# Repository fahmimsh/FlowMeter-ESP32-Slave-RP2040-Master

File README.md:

# FlowMeter-ESP32-Slave-RP2040-Master

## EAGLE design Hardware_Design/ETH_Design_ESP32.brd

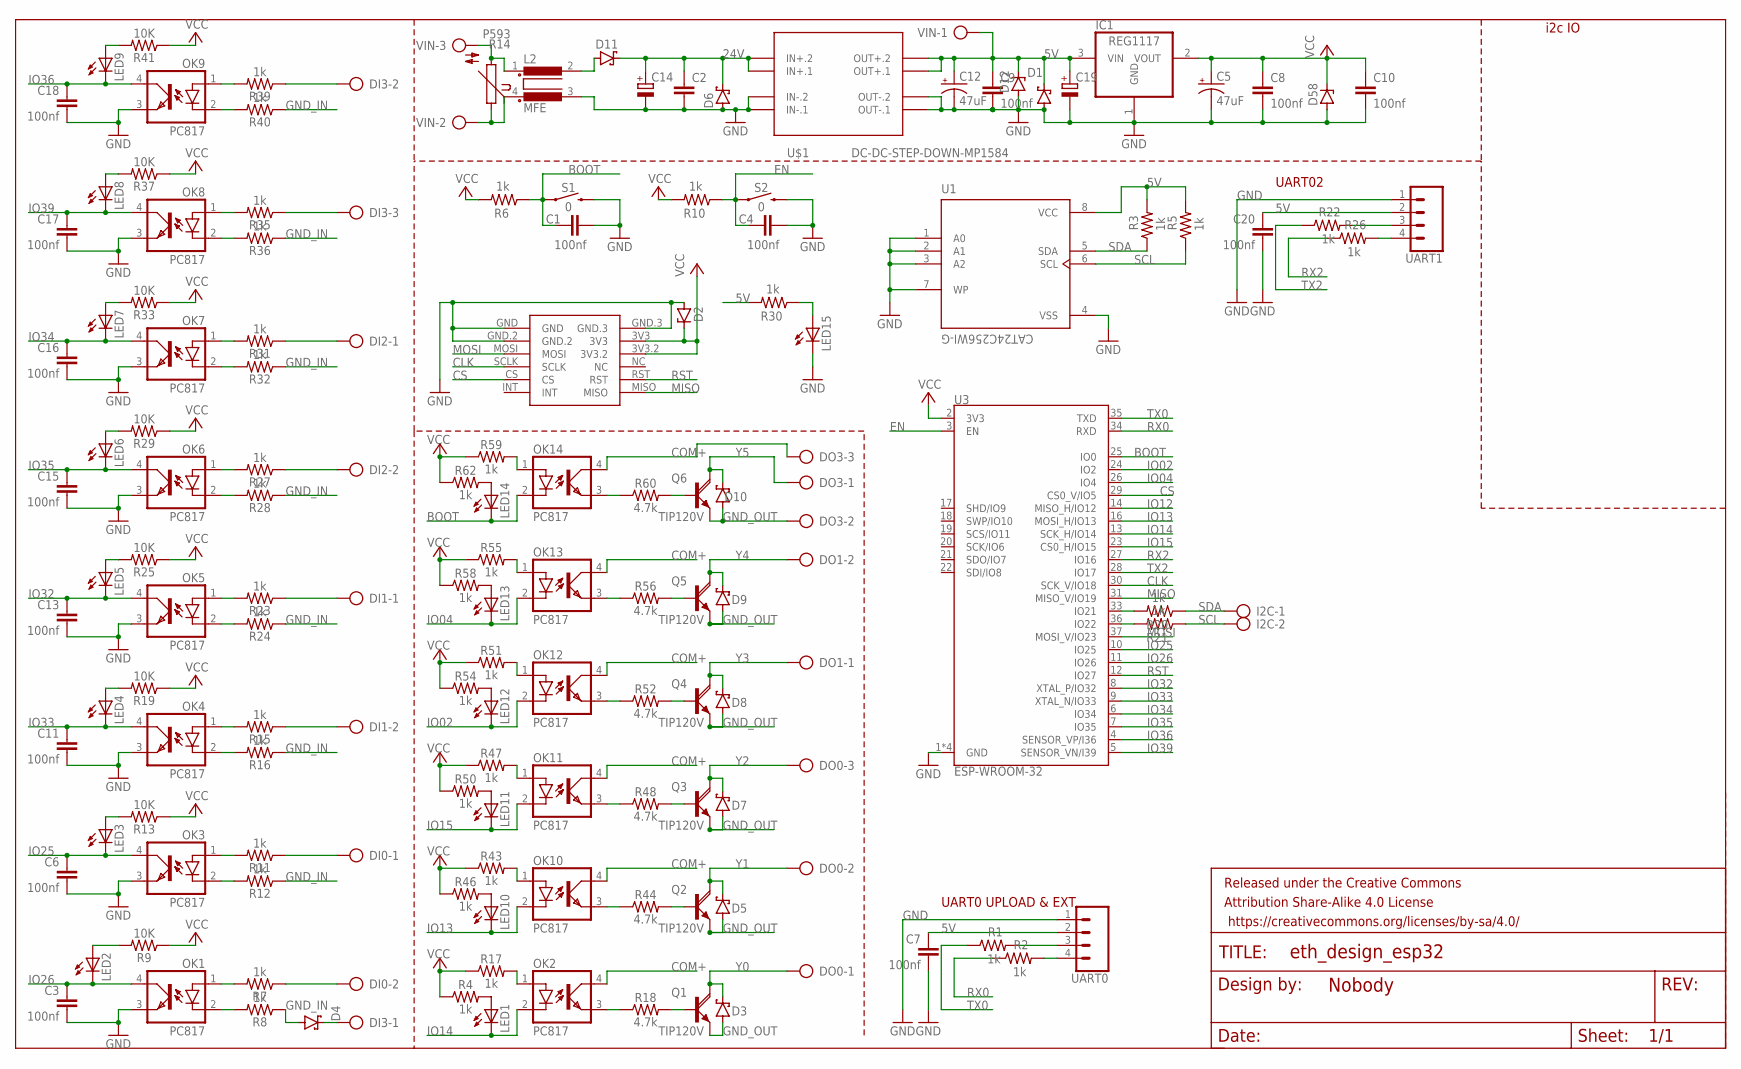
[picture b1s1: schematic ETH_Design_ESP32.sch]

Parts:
C1, C3, C4, C6, C7, C8, C9, C10, C11, C13, C15, C16, C17, C18, C20: 100nf; 0805
C2: C-EUC1206K; C1206K
C5, C12: 47uF; EIA3528
C14, C19: CPOL-EUE2.5-7; E2,5-7
D1, D3, D4, D5, D6, D7, D8, D9, D10, D11: SCHOTTKY-DIODESMD; SMB
D2, D12, D58: ZENER-DIODESOD80C; SOD80C
DI0, DI1, DI2: AK500/2
DI3: AK500/3
DO0, DO3: AK500/3
DO1: AK500/2
FRAME1: FRAME-LETTERNO_PACKAGE; DUMMY
I2C: AK500/2
IC1: REG1117; SOT223
L2: MFE
LED1, LED2, LED3, LED4, LED5, LED6, LED7, LED8, LED9, LED10, LED11, LED12, LED13, LED14, LED15: LEDCHIPLED_0805; CHIPLED_0805
OK1, OK2, OK3, OK4, OK5, OK6, OK7, OK8, OK9, OK10, OK11, OK12, OK13, OK14: PC817; DIL04
Q1, Q2, Q3, Q4, Q5, Q6: TIP120V; TO220AV
R1, R2, R3, R4, R5, R6, R7, R8, R10, R11, R12, R15, R16, R17, R20, R21, R22, R23, R24, R26, R27, R28, R30, R31, R32, R35, R36, R39, R40, R43, R46, R47, R50, R51, R54, R55, R58, R59, R62: 1k; 0805
R9, R13, R19, R25, R29, R33, R37, R41: 10K; 0805
R14: P593
R18, R44, R48, R52, R56, R60: 4.7k; 0805
S1, S2: 0; TACTILE_SWITCH_PTH_6.0MM_KIT
U1: CAT24C256WI-G; SOIC127P600X175-8N
U3: ESP-WROOM-32
U$1: DC-DC-STEP-DOWN-MP1584
U$2: MINI_W5500
UART0, UART1: CONN_04POLAR; MOLEX-1X4
VIN: AK500/3

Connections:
5V: C7.1, C9.1, C12.A (+), C19.+, C20.1, D1.C, D12.C, IC1.3 (VIN), R3.2, R5.2, R30.2, U1.8 (VCC), U$1.OUT+.1, U$1.OUT+.2, UART0.2, UART1.2, VIN.1
24V: C2.1, C14.+, D6.C, D11.C, U$1.IN+.1, U$1.IN+.2
BOOT: C1.2, LED14.C, OK14.2 (C), R6.1, S1.1, U3.25 (IO0)
CLK: U3.30 (SCK_V/IO18), U$2.SCLK
COM+: DO3.3, OK2.4 (COL), OK10.4 (COL), OK11.4 (COL), OK12.4 (COL), OK13.4 (COL), OK14.4 (COL)
CS: U3.29 (CS0_V/IO5), U$2.CS
EN: C4.2, R10.1, S2.1, U3.3 (EN)
GND: C1.1, C2.2, C3.2, C4.1, C5.C (-), C6.2, C7.2, C8.2, C9.2, C10.2, C11.2, C12.C (-), C13.2, C14.-, C15.2, C16.2, C17.2, C18.2, C19.-, C20.2, D1.A, D2.A, D6.A, D12.A, D58.A, IC1.1 (GND), L2.3 (4), LED15.C, OK1.3 (EMIT), OK3.3 (EMIT), OK4.3 (EMIT), OK5.3 (EMIT), OK6.3 (EMIT), OK7.3 (EMIT), OK8.3 (EMIT), OK9.3 (EMIT), S1.3 (2), S2.3 (2), U1.1 (A0), U1.2 (A1), U1.3 (A2), U1.4 (VSS), U1.7 (WP), U3.1 (GND), U3.15 (GND), U3.38 (GND), U3.GND, U$1.IN-.1, U$1.IN-.2, U$1.OUT-.1, U$1.OUT-.2, U$2.GND, U$2.GND.2, U$2.GND.3, UART0.1, UART1.1
GND_IN: D4.A, R8.1, R12.1, R16.1, R24.1, R28.1, R32.1, R36.1, R40.1
GND_OUT: D3.A, D5.A, D7.A, D8.A, D9.A, D10.A, DO3.2, Q1.E, Q2.E, Q3.E, Q4.E, Q5.E, Q6.E
IO02: LED12.C, OK12.2 (C), U3.24 (IO2)
IO04: LED13.C, OK13.2 (C), U3.26 (IO4)
IO12: U3.14 (MISO_H/IO12)
IO13: LED10.C, OK10.2 (C), U3.16 (MOSI_H/IO13)
IO14: LED1.C, OK2.2 (C), U3.13 (SCK_H/IO14)
IO15: LED11.C, OK11.2 (C), U3.23 (CS0_H/IO15)
IO25: C6.1, LED3.C, OK3.4 (COL), U3.10 (IO25)
IO26: C3.1, LED2.C, OK1.4 (COL), U3.11 (IO26)
IO32: C13.1, LED5.C, OK5.4 (COL), U3.8 (XTAL_P/IO32)
IO33: C11.1, LED4.C, OK4.4 (COL), U3.9 (XTAL_N/IO33)
IO34: C16.1, LED7.C, OK7.4 (COL), U3.6 (IO34)
IO35: C15.1, LED6.C, OK6.4 (COL), U3.7 (IO35)
IO36: C18.1, LED9.C, OK9.4 (COL), U3.4 (SENSOR_VP/I36)
IO39: C17.1, LED8.C, OK8.4 (COL), U3.5 (SENSOR_VN/I39)
MISO: U3.31 (MISO_V/IO19), U$2.MISO
MOSI: U3.37 (MOSI_V/IO23), U$2.MOSI
unnamed: R1.2, UART0.3
unnamed: R2.2, UART0.4
unnamed: R22.2, UART1.3
unnamed: OK1.1 (A), R7.2
unnamed: L2.1, R14.2, VIN.3
unnamed: L2.4 (3), R14.1, VIN.2
unnamed: OK2.1 (A), R17.2
unnamed: LED1.A, R4.2
unnamed: LED8.A, R37.2
unnamed: OK1.2 (C), R8.2
unnamed: LED7.A, R33.2
unnamed: LED6.A, R29.2
unnamed: LED5.A, R25.2
unnamed: R26.2, UART1.4
unnamed: LED15.A, R30.1
unnamed: OK3.1 (A), R11.2
unnamed: OK2.3 (EMIT), R18.1
unnamed: D11.A, L2.2
unnamed: OK3.2 (C), R12.2
unnamed: LED2.A, R9.2
unnamed: LED3.A, R13.2
unnamed: OK4.1 (A), R15.2
unnamed: OK4.2 (C), R16.2
unnamed: LED4.A, R19.2
unnamed: R20.2, U3.33 (IO21)
unnamed: R21.2, U3.36 (IO22)
unnamed: OK5.1 (A), R23.2
unnamed: OK5.2 (C), R24.2
unnamed: OK6.1 (A), R27.2
unnamed: OK6.2 (C), R28.2
unnamed: OK7.1 (A), R31.2
unnamed: OK7.2 (C), R32.2
unnamed: OK8.1 (A), R35.2
unnamed: OK8.2 (C), R36.2
unnamed: OK9.1 (A), R39.2
unnamed: OK9.2 (C), R40.2
unnamed: DI0.2, R7.1
unnamed: Q1.B, R18.2
unnamed: OK10.3 (EMIT), R44.1
unnamed: OK10.1 (A), R43.2
unnamed: LED10.A, R46.2
unnamed: Q2.B, R44.2
unnamed: OK11.3 (EMIT), R48.1
unnamed: OK11.1 (A), R47.2
unnamed: LED11.A, R50.2
unnamed: Q3.B, R48.2
unnamed: OK12.3 (EMIT), R52.1
unnamed: OK12.1 (A), R51.2
unnamed: LED12.A, R54.2
unnamed: LED9.A, R41.2
unnamed: Q4.B, R52.2
unnamed: OK13.3 (EMIT), R56.1
unnamed: DI0.1, R11.1
unnamed: OK13.1 (A), R55.2
unnamed: LED13.A, R58.2
unnamed: DI1.2, R15.1
unnamed: Q5.B, R56.2
unnamed: OK14.3 (EMIT), R60.1
unnamed: DI1.1, R23.1
unnamed: OK14.1 (A), R59.2
unnamed: LED14.A, R62.2
unnamed: DI2.2, R27.1
unnamed: Q6.B, R60.2
unnamed: DI2.1, R31.1
unnamed: DI3.3, R35.1
unnamed: DI3.2, R39.1
unnamed: D4.C, DI3.1
RST: U3.12 (IO27), U$2.RST
RX0: R2.1, U3.34 (RXD)
RX2: R26.1, U3.27 (IO16)
SCL: I2C.2, R5.1, R21.1, U1.6 (SCL)
SDA: I2C.1, R3.1, R20.1, U1.5 (SDA)
TX0: R1.1, U3.35 (TXD)
TX2: R22.1, U3.28 (IO17)
VCC: C5.A (+), C8.1, C10.1, D2.C, D58.C, IC1.2 (VOUT), R4.1, R6.2, R9.1, R10.2, R13.1, R17.1, R19.1, R25.1, R29.1, R33.1, R37.1, R41.1, R43.1, R46.1, R47.1, R50.1, R51.1, R54.1, R55.1, R58.1, R59.1, R62.1, U3.2 (3V3), U$2.3V3, U$2.3V3.2
Y0: D3.C, DO0.1, Q1.C
Y1: D5.C, DO0.2, Q2.C
Y2: D7.C, DO0.3, Q3.C
Y3: D8.C, DO1.1, Q4.C
Y4: D9.C, DO1.2, Q5.C
Y5: D10.C, DO3.1, Q6.C

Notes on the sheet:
UART0 UPLOAD & EXT
i2c IO
UART02

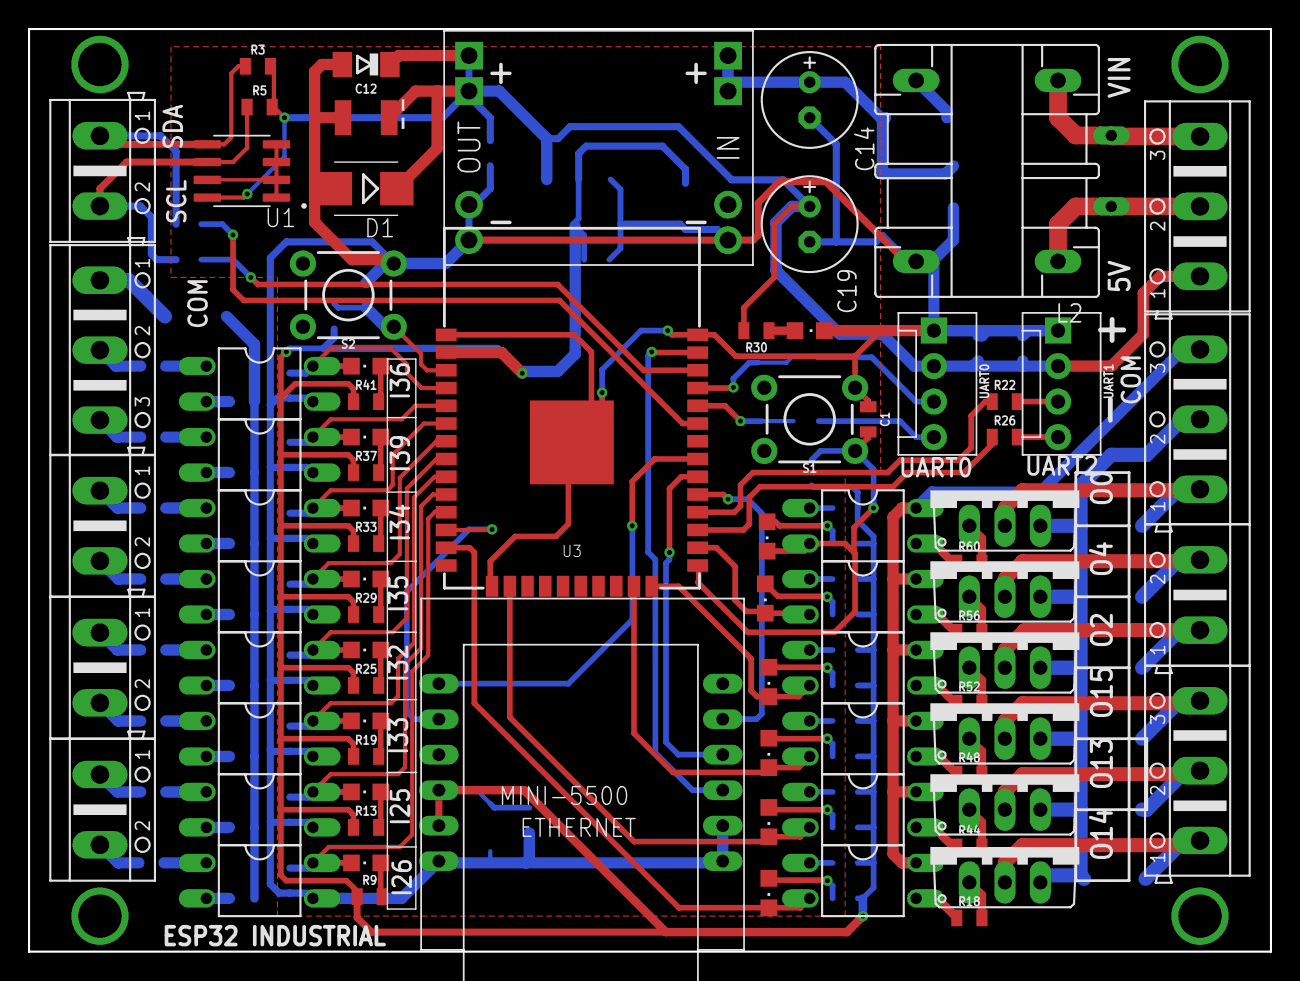
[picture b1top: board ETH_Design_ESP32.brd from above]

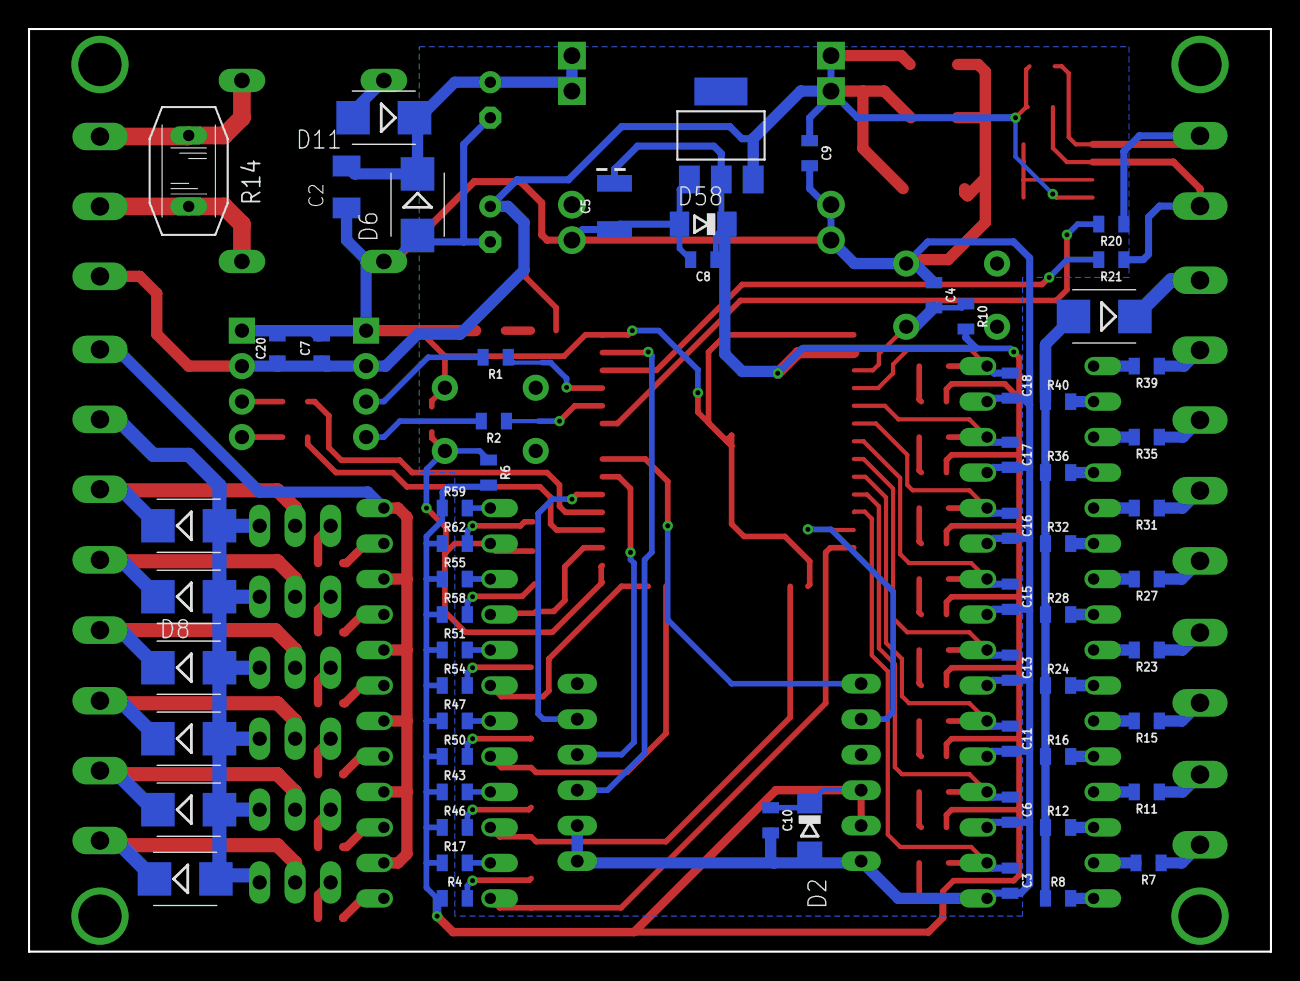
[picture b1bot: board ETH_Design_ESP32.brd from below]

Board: 2 copper layers, 88.9 x 66.0 mm, 142 parts (63 on the bottom side), 106 nets.

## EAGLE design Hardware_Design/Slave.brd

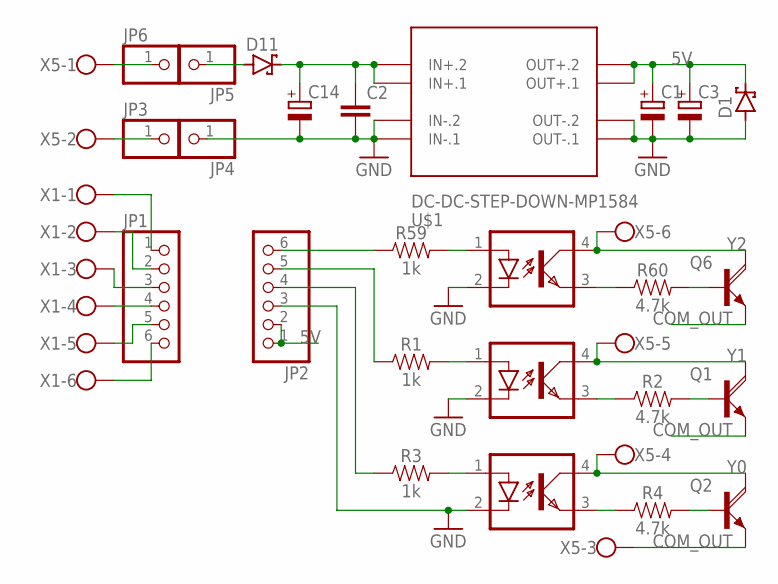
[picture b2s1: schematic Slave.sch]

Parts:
C1, C3, C14: CPOL-EUE2.5-7; E2,5-7
C2: C-EUC1206K; C1206K
D1, D11: SCHOTTKY-DIODESMD; SMB
JP1, JP2: PINHD-1X6B; 1X06-BIG
JP3, JP4, JP5, JP6: PINHD-1X1; 1X01
OK1, OK2, OK14: PC817; DIL04
Q1, Q2, Q6: TIP120V; TO220AV
R1, R3, R59: 1k; 0805
R2, R4, R60: 4.7k; 0805
U$1: DC-DC-STEP-DOWN-MP1584
X1, X5: W237-136

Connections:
5V: C1.+, C3.+, D1.C, JP2.1, JP2.2, U$1.OUT+.1, U$1.OUT+.2
COM_OUT: Q1.E, Q2.E, Q6.E, X5.3
GND: C1.-, C2.2, C3.-, C14.-, D1.A, JP2.3, JP4.1, OK1.2 (C), OK2.2 (C), OK14.2 (C), U$1.IN-.1, U$1.IN-.2, U$1.OUT-.1, U$1.OUT-.2
unnamed: OK1.3 (EMIT), R2.1
unnamed: OK1.1 (A), R1.2
unnamed: Q1.B, R2.2
unnamed: OK2.3 (EMIT), R4.1
unnamed: OK2.1 (A), R3.2
unnamed: Q2.B, R4.2
unnamed: JP1.6, X1.6
unnamed: JP1.5, X1.5
unnamed: JP1.4, X1.4
unnamed: JP1.3, X1.3
unnamed: JP1.2, X1.2
unnamed: JP1.1, X1.1
unnamed: JP2.6, R59.1
unnamed: JP2.5, R1.1
unnamed: JP2.4, R3.1
unnamed: D11.A, JP5.1
unnamed: JP3.1, X5.2
unnamed: JP6.1, X5.1
unnamed: C2.1, C14.+, D11.C, U$1.IN+.1, U$1.IN+.2
unnamed: OK14.3 (EMIT), R60.1
unnamed: OK14.1 (A), R59.2
unnamed: Q6.B, R60.2
Y0: OK2.4 (COL), Q2.C, X5.4
Y1: OK1.4 (COL), Q1.C, X5.5
Y2: OK14.4 (COL), Q6.C, X5.6

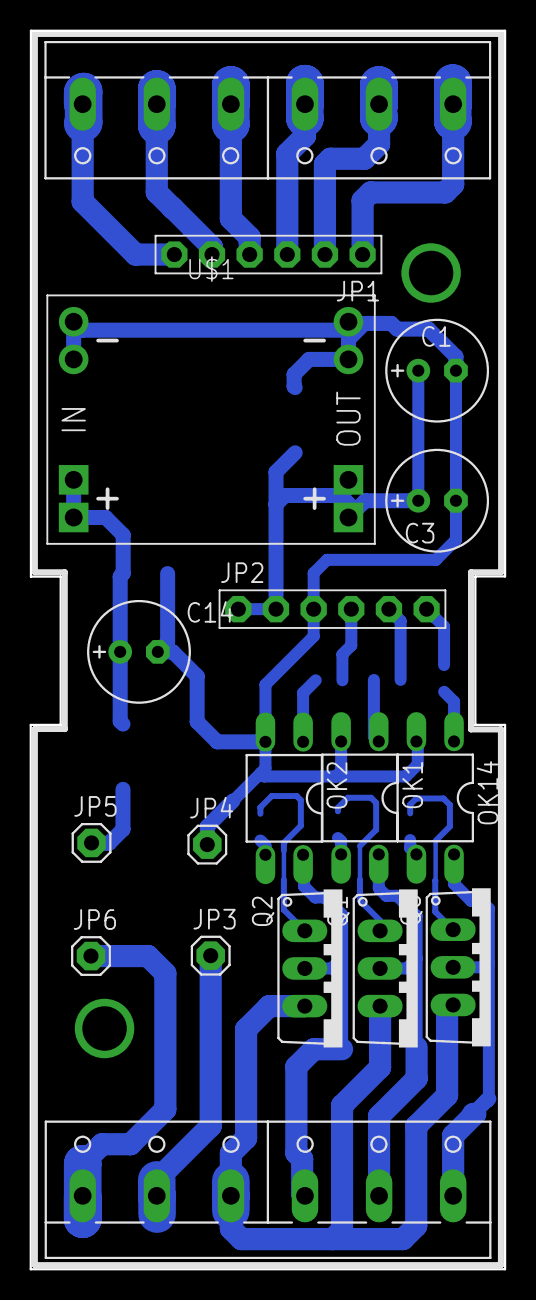
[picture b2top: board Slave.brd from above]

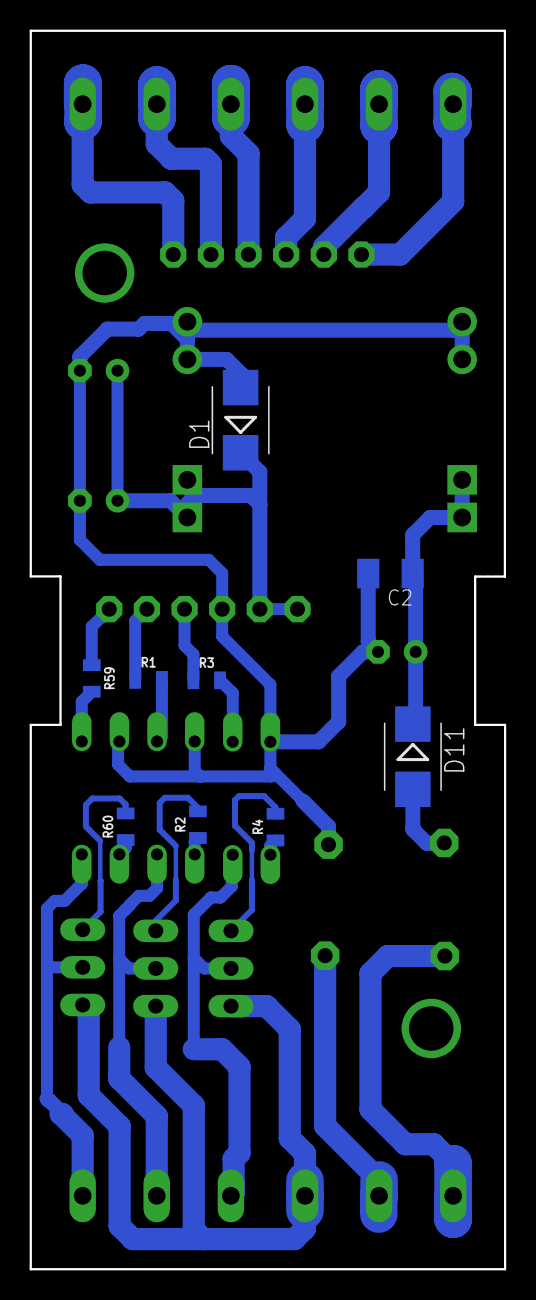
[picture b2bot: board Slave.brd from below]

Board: 2 copper layers, 32.0 x 83.6 mm, 27 parts (9 on the bottom side), 28 nets.

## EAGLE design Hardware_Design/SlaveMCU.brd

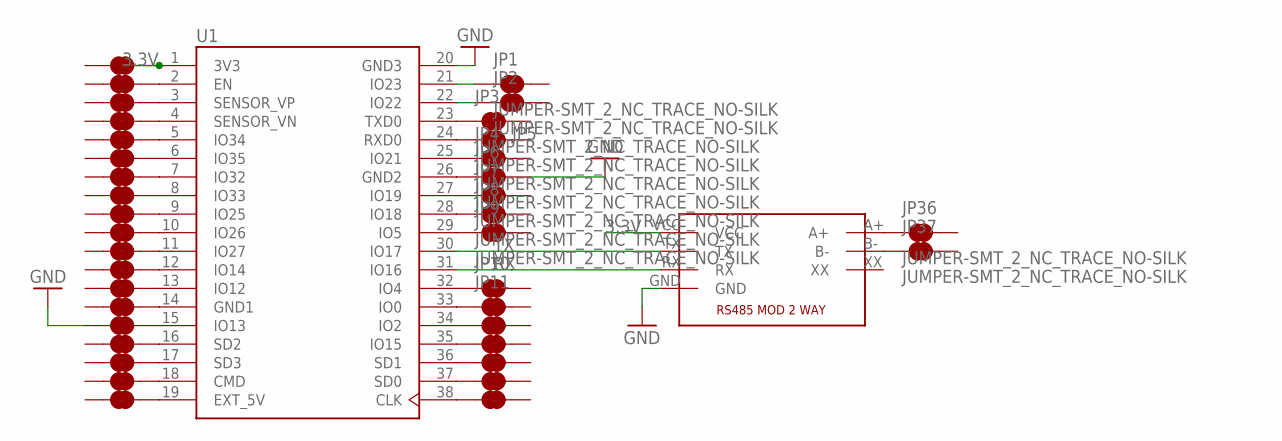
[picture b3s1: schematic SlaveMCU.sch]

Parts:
JP1, JP2, JP3, JP4, JP5, JP6, JP7, JP8, JP9, JP10, JP11, JP12, JP13, JP14, JP15, JP16, JP17, JP18, JP19, JP20, JP21, JP22, JP23, JP24, JP25, JP26, JP27, JP28, JP29, JP30, JP31, JP32, JP33, JP34, JP35, JP36, JP37: JUMPER-SMT_2_NC_TRACE_NO-SILK; SMT-JUMPER_2_NC_TRACE_NO-SILK
U1: ESP32-DEVKITC-32D; MODULE_ESP32-DEVKITC-32D
U$2: RS485_MODULE

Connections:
3.3V: JP35.2, U1.1 (3V3), U$2.VCC
GND: JP6.2, JP21.1, U1.20 (GND3), U$2.GND
unnamed: JP1.1, U1.21 (IO23)
unnamed: JP4.1, U1.25 (IO21)
unnamed: JP5.1, U1.24 (RXD0)
unnamed: JP6.1, U1.26 (GND2)
unnamed: JP7.1, U1.27 (IO19)
unnamed: JP9.1, U1.29 (IO5)
unnamed: JP10.1, U1.32 (IO4)
unnamed: JP11.1, U1.33 (IO0)
unnamed: JP12.1, U1.34 (IO2)
unnamed: JP13.1, U1.35 (IO15)
unnamed: JP14.1, U1.36 (SD1)
unnamed: JP15.1, U1.37 (SD0)
unnamed: JP16.1, U1.38 (CLK)
unnamed: JP17.2, U1.19 (EXT_5V)
unnamed: JP18.2, U1.18 (CMD)
unnamed: JP19.2, U1.17 (SD3)
unnamed: JP20.2, U1.16 (SD2)
unnamed: JP21.2, U1.15 (IO13)
unnamed: JP22.2, U1.14 (GND1)
unnamed: JP23.2, U1.13 (IO12)
unnamed: JP24.2, U1.12 (IO14)
unnamed: JP26.2, U1.10 (IO26)
unnamed: JP27.2, U1.9 (IO25)
unnamed: JP28.2, U1.8 (IO33)
unnamed: JP29.2, U1.7 (IO32)
unnamed: JP30.2, U1.5 (IO34)
unnamed: JP31.2, U1.6 (IO35)
unnamed: JP32.2, U1.4 (SENSOR_VN)
unnamed: JP33.2, U1.3 (SENSOR_VP)
unnamed: JP34.2, U1.2 (EN)
unnamed: JP25.2, U1.11 (IO27)
unnamed: JP8.1, U1.28 (IO18)
unnamed: JP3.1, U1.23 (TXD0)
unnamed: JP2.1, U1.22 (IO22)
unnamed: JP36.1, U$2.A+
unnamed: JP37.1, U$2.B-
RX: U1.31 (IO16), U$2.RX
TX: U1.30 (IO17), U$2.TX

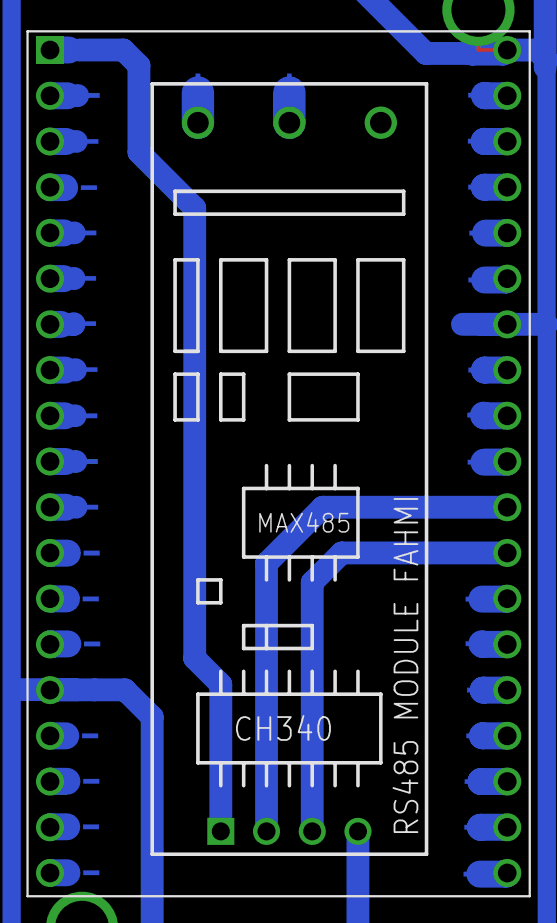
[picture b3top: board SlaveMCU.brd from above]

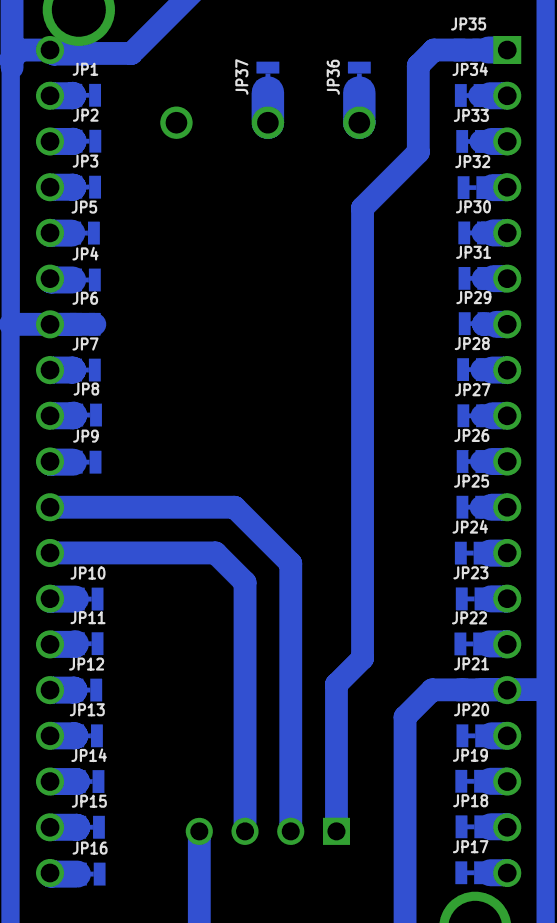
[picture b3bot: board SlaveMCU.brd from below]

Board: 2 copper layers, 39 parts (37 on the bottom side), 40 nets.

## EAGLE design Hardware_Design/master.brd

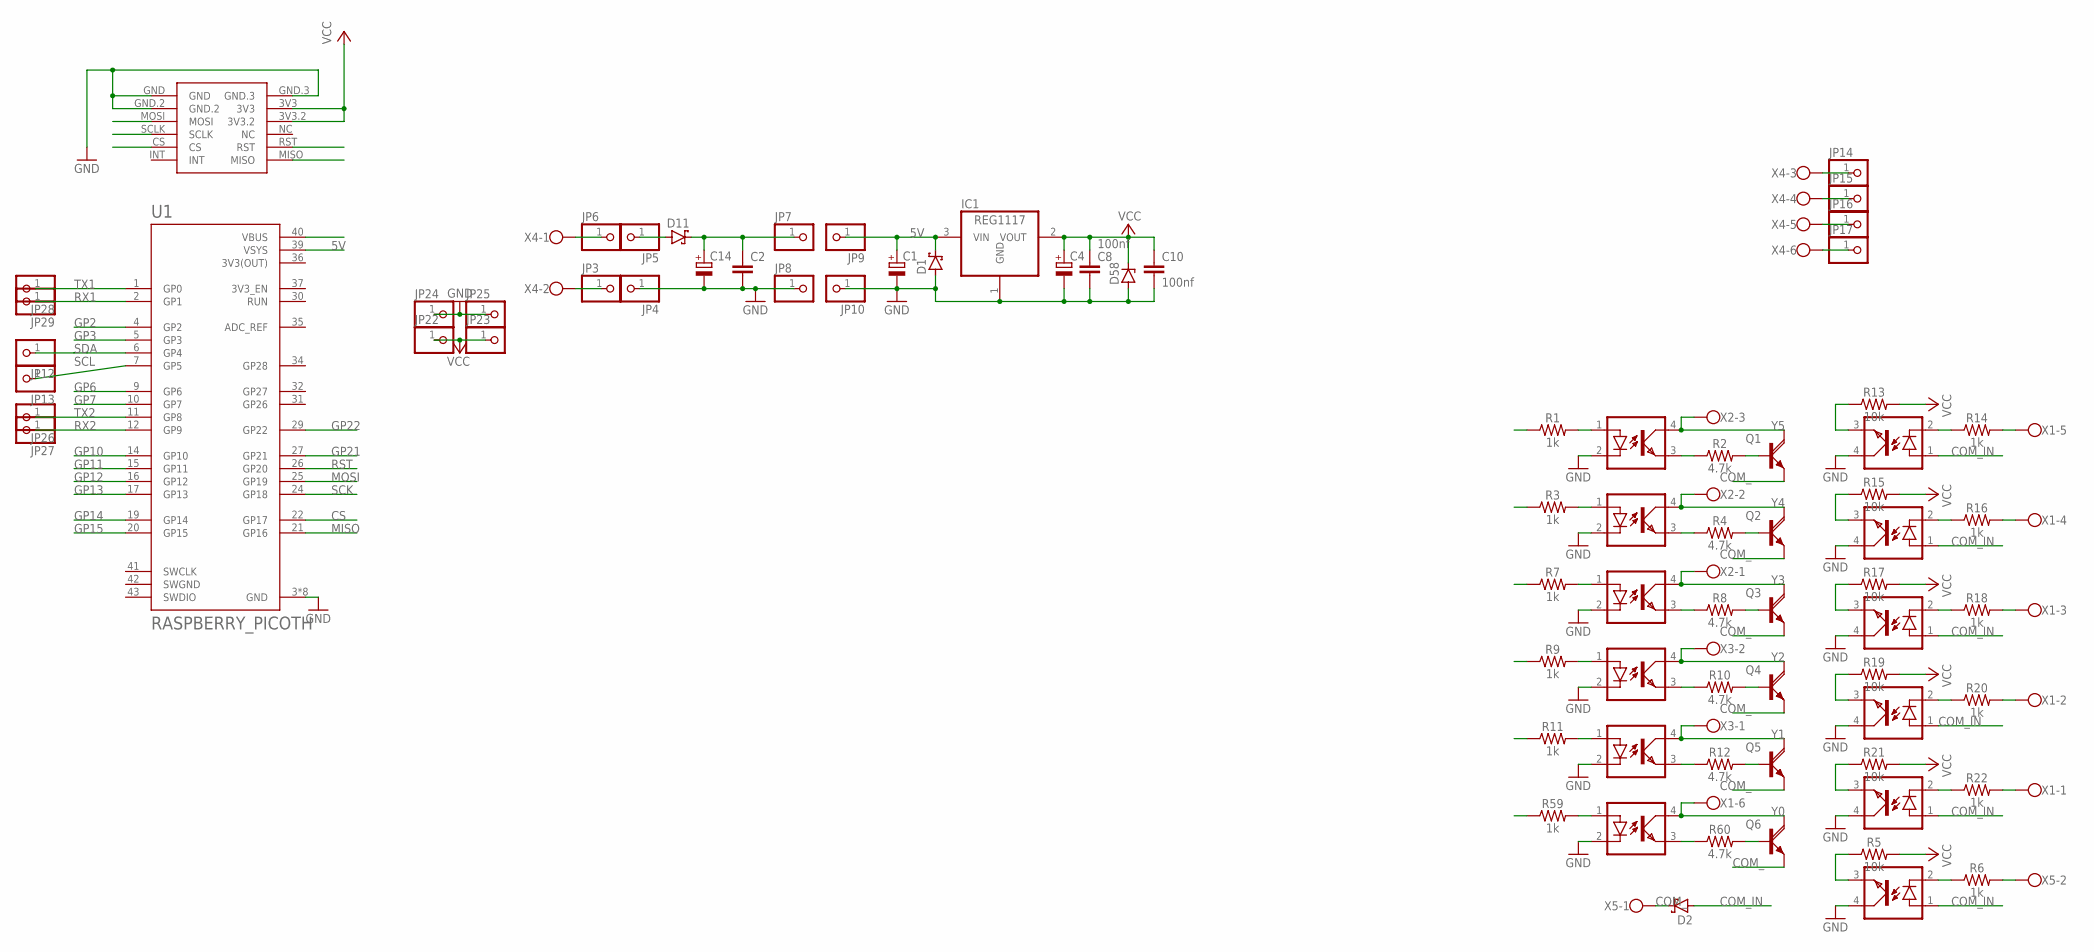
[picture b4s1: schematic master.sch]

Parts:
C1, C4, C14: CPOL-EUE2.5-7; E2,5-7
C2: C-EUC1206K; C1206K
C8, C10: 100nf; 0805
D1, D2, D11: SCHOTTKY-DIODESMD; SMB
D58: ZENER-DIODESOD80C; SOD80C
IC1: REG1117; SOT223
JP3, JP4, JP5, JP6, JP7, JP8, JP9, JP10, JP12, JP13, JP14, JP15, JP16, JP17, JP22, JP23, JP24, JP25, JP26, JP27, JP28, JP29: PINHD-1X1; 1X01
OK1, OK2, OK3, OK4, OK5, OK6, OK7, OK8, OK9, OK10, OK11, OK14: PC817; DIL04
Q1, Q2, Q3, Q4, Q5, Q6: TIP120V; TO220AV
R1, R3, R6, R7, R9, R11, R14, R16, R18, R20, R22, R59: 1k; 0805
R2, R4, R8, R10, R12, R60: 4.7k; 0805
R5, R13, R15, R17, R19, R21: 10k; 0805
U1: RASPBERRY_PICOTH; PICO-PKG-TH
U$2: MINI_W5500
X1, X4: W237-136
X2: W237-103
X3, X5: W237-102

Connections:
3V3(OUT): U1.36 (3V3(OUT))
5V: C1.+, D1.C, IC1.3 (VIN), JP9.1, U1.39 (VSYS)
COM_: D2.C, Q1.E, Q2.E, Q3.E, Q4.E, Q5.E, Q6.E, X5.1
COM_IN: D2.A, OK3.1 (A), OK7.1 (A), OK8.1 (A), OK9.1 (A), OK10.1 (A), OK11.1 (A)
CS: U1.22 (GP17)
GND: C1.-, C2.2, C4.-, C8.2, C10.2, C14.-, D1.A, D58.A, IC1.1 (GND), JP4.1, JP8.1, JP10.1, JP24.1, JP25.1, OK1.2 (C), OK2.2 (C), OK3.4 (COL), OK4.2 (C), OK5.2 (C), OK6.2 (C), OK7.4 (COL), OK8.4 (COL), OK9.4 (COL), OK10.4 (COL), OK11.4 (COL), OK14.2 (C), U1.3 (GND), U1.8 (GND), U1.13 (GND), U1.18 (GND), U1.23 (GND), U1.28 (GND), U1.33 (GND), U1.38 (GND), U$2.GND, U$2.GND.2, U$2.GND.3
GP2: U1.4 (GP2)
GP3: U1.5 (GP3)
GP6: U1.9 (GP6)
GP7: U1.10 (GP7)
GP10: U1.14 (GP10)
GP11: U1.15 (GP11)
GP12: U1.16 (GP12)
GP13: U1.17 (GP13)
GP14: U1.19 (GP14)
GP15: U1.20 (GP15)
GP21: U1.27 (GP21)
GP22: U1.29 (GP22)
MISO: U1.21 (GP16)
MOSI: U1.25 (GP19)
unnamed: OK1.3 (EMIT), R2.1
unnamed: OK1.1 (A), R1.2
unnamed: Q1.B, R2.2
unnamed: OK2.3 (EMIT), R4.1
unnamed: OK2.1 (A), R3.2
unnamed: Q2.B, R4.2
unnamed: OK8.2 (C), R16.1
unnamed: OK9.2 (C), R18.1
unnamed: OK4.3 (EMIT), R8.1
unnamed: OK4.1 (A), R7.2
unnamed: Q3.B, R8.2
unnamed: OK5.3 (EMIT), R10.1
unnamed: OK5.1 (A), R9.2
unnamed: Q4.B, R10.2
unnamed: OK6.3 (EMIT), R12.1
unnamed: JP6.1, X4.1
unnamed: D11.A, JP5.1
unnamed: JP3.1, X4.2
unnamed: OK6.1 (A), R11.2
unnamed: Q5.B, R12.2
unnamed: C2.1, C14.+, D11.C, JP7.1
unnamed: OK7.2 (C), R14.1
unnamed: OK10.2 (C), R20.1
unnamed: OK11.2 (C), R22.1
unnamed: OK3.2 (C), R6.1
unnamed: OK7.3 (EMIT), R13.1
unnamed: OK8.3 (EMIT), R15.1
unnamed: OK9.3 (EMIT), R17.1
unnamed: OK10.3 (EMIT), R19.1
unnamed: JP14.1, X4.3
unnamed: JP15.1, X4.4
unnamed: JP16.1, X4.5
unnamed: JP17.1, X4.6
unnamed: OK11.3 (EMIT), R21.1
unnamed: OK3.3 (EMIT), R5.1
unnamed: R14.2, X1.5
unnamed: R16.2, X1.4
unnamed: R18.2, X1.3
unnamed: R20.2, X1.2
unnamed: R22.2, X1.1
unnamed: R6.2, X5.2
unnamed: OK14.3 (EMIT), R60.1
unnamed: OK14.1 (A), R59.2
unnamed: Q6.B, R60.2
RST: U1.26 (GP20)
RX1: JP29.1, U1.2 (GP1)
RX2: JP27.1, U1.12 (GP9)
SCK: U1.24 (GP18)
SCL: JP13.1, U1.7 (GP5)
SDA: JP12.1, U1.6 (GP4)
SWGND: U1.42 (SWGND)
TX1: JP28.1, U1.1 (GP0)
TX2: JP26.1, U1.11 (GP8)
VCC: C4.+, C8.1, C10.1, D58.C, IC1.2 (VOUT), JP22.1, JP23.1, R5.2, R13.2, R15.2, R17.2, R19.2, R21.2, U$2.3V3, U$2.3V3.2
Y0: OK14.4 (COL), Q6.C, X1.6
Y1: OK6.4 (COL), Q5.C, X3.1
Y2: OK5.4 (COL), Q4.C, X3.2
Y3: OK4.4 (COL), Q3.C, X2.1
Y4: OK2.4 (COL), Q2.C, X2.2
Y5: OK1.4 (COL), Q1.C, X2.3

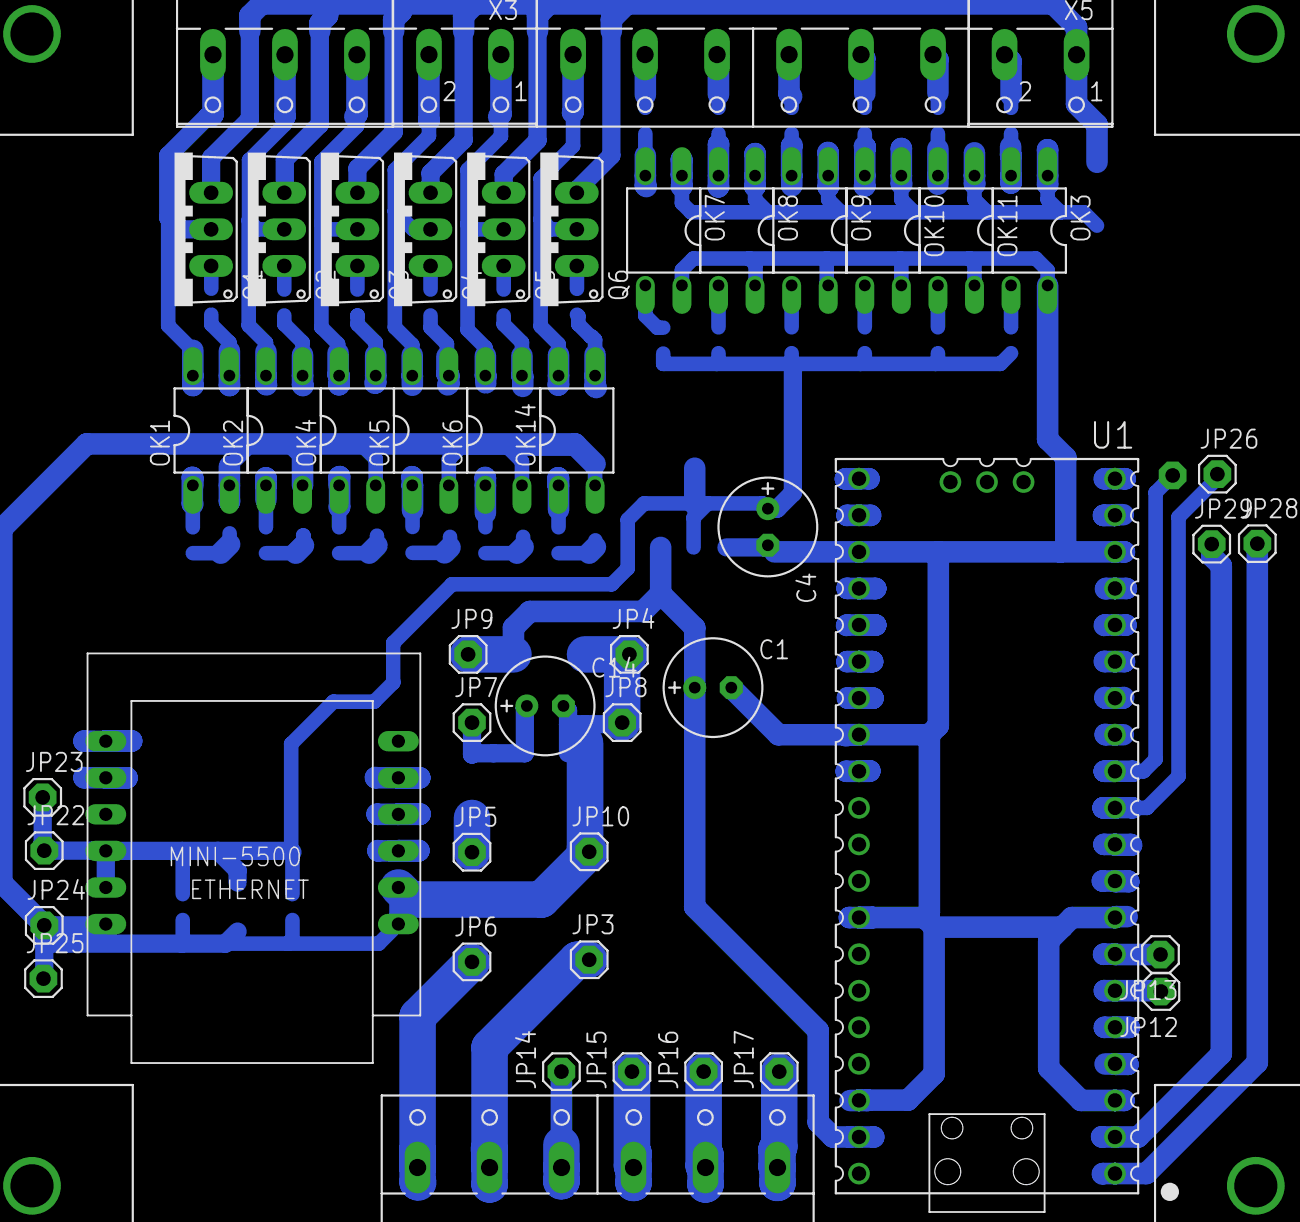
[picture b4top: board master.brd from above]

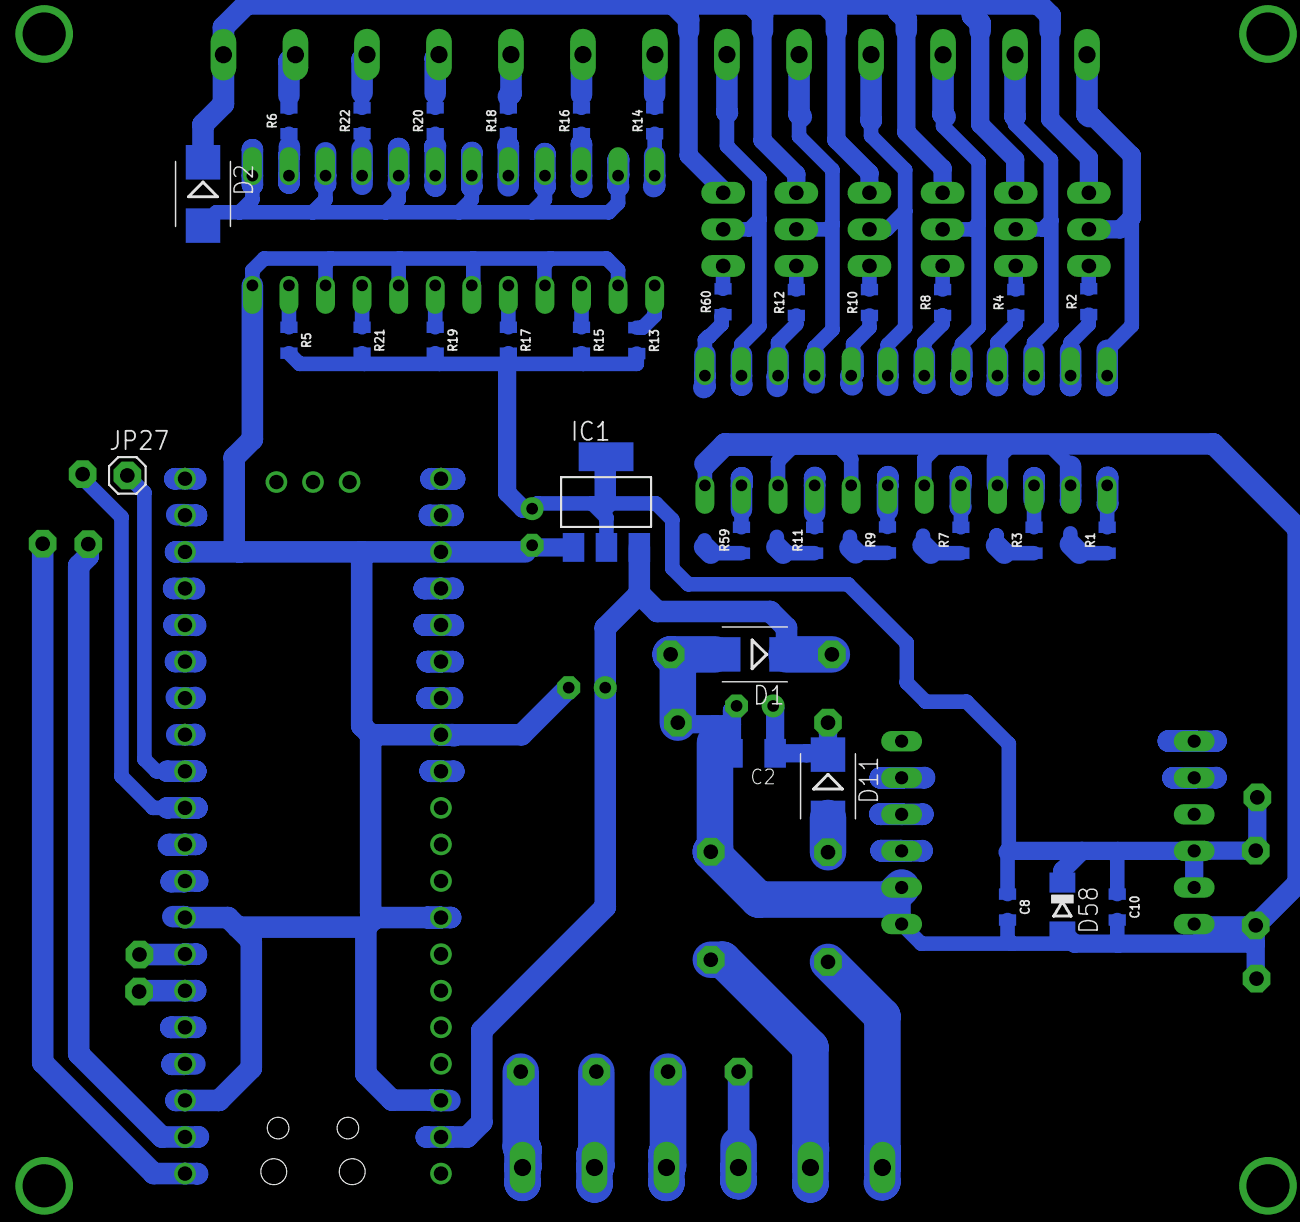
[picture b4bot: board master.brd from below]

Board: 2 copper layers, 82 parts (33 on the bottom side), 61 nets.

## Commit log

2024-01-31 add-DesainHardware
2024-02-02 Simplify-Code1
2024-02-02 simplify-opc2
2024-02-03 opc-ok
2024-02-03 add-modbus-TCP
2024-02-06 nmbsGateWay
2024-02-11 fixChangeMb
2024-02-11 delChange
2024-02-11 flush
2024-02-12 scada
2024-02-12 cobaChangedClientFlush
2024-02-12 clientStopadded
2024-02-12 opcAdd
2024-02-22 scada_hmi
2024-02-22 path
2024-02-23 addScada
2024-02-23 fl1_sd_fl4
2024-02-24 data_logger
2024-02-28 add fl2 lama
2024-02-29 revisi_esp32
2024-03-05 scada_fl2
2024-03-16 flow_meter_nextion_ok
2024-05-06 changed
2024-05-12 new_
2024-05-18 change library
2024-05-19 set_platformio
2024-06-03 update scada
2024-11-11 CHNGED
2024-11-11 add flow meter
2025-02-08 CHANGE

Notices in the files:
parts and their libraries:
SparkFun-Capacitors: Licensing: Creative Commons ShareAlike 4.0 International - https://creativecommons.org/licenses/by-sa/4.0
diy-modules: Released under the Creative Commons Attribution 4.0 International License: http://creativecommons.org/licenses/by/4.0
